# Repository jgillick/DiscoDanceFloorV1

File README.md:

# Disco Dance Floor

This project is for a full-size interactive dance floor that can respond to touch and sound.

The floor is made up of individually controlled squares (nodes) attached to a computer via an
RS485 bus. Each node has an Atmega328 with RGB LEDs and a capacitive sensor to detect someone
standing over that cell.

The master controller uses Node.js and provides a simple API that can be used to
write custom floor control programs.

## More information
More information about the build can be found on my page at [hackaday.io](https://hackaday.io/project/4209-interactive-disco-dance-floor).

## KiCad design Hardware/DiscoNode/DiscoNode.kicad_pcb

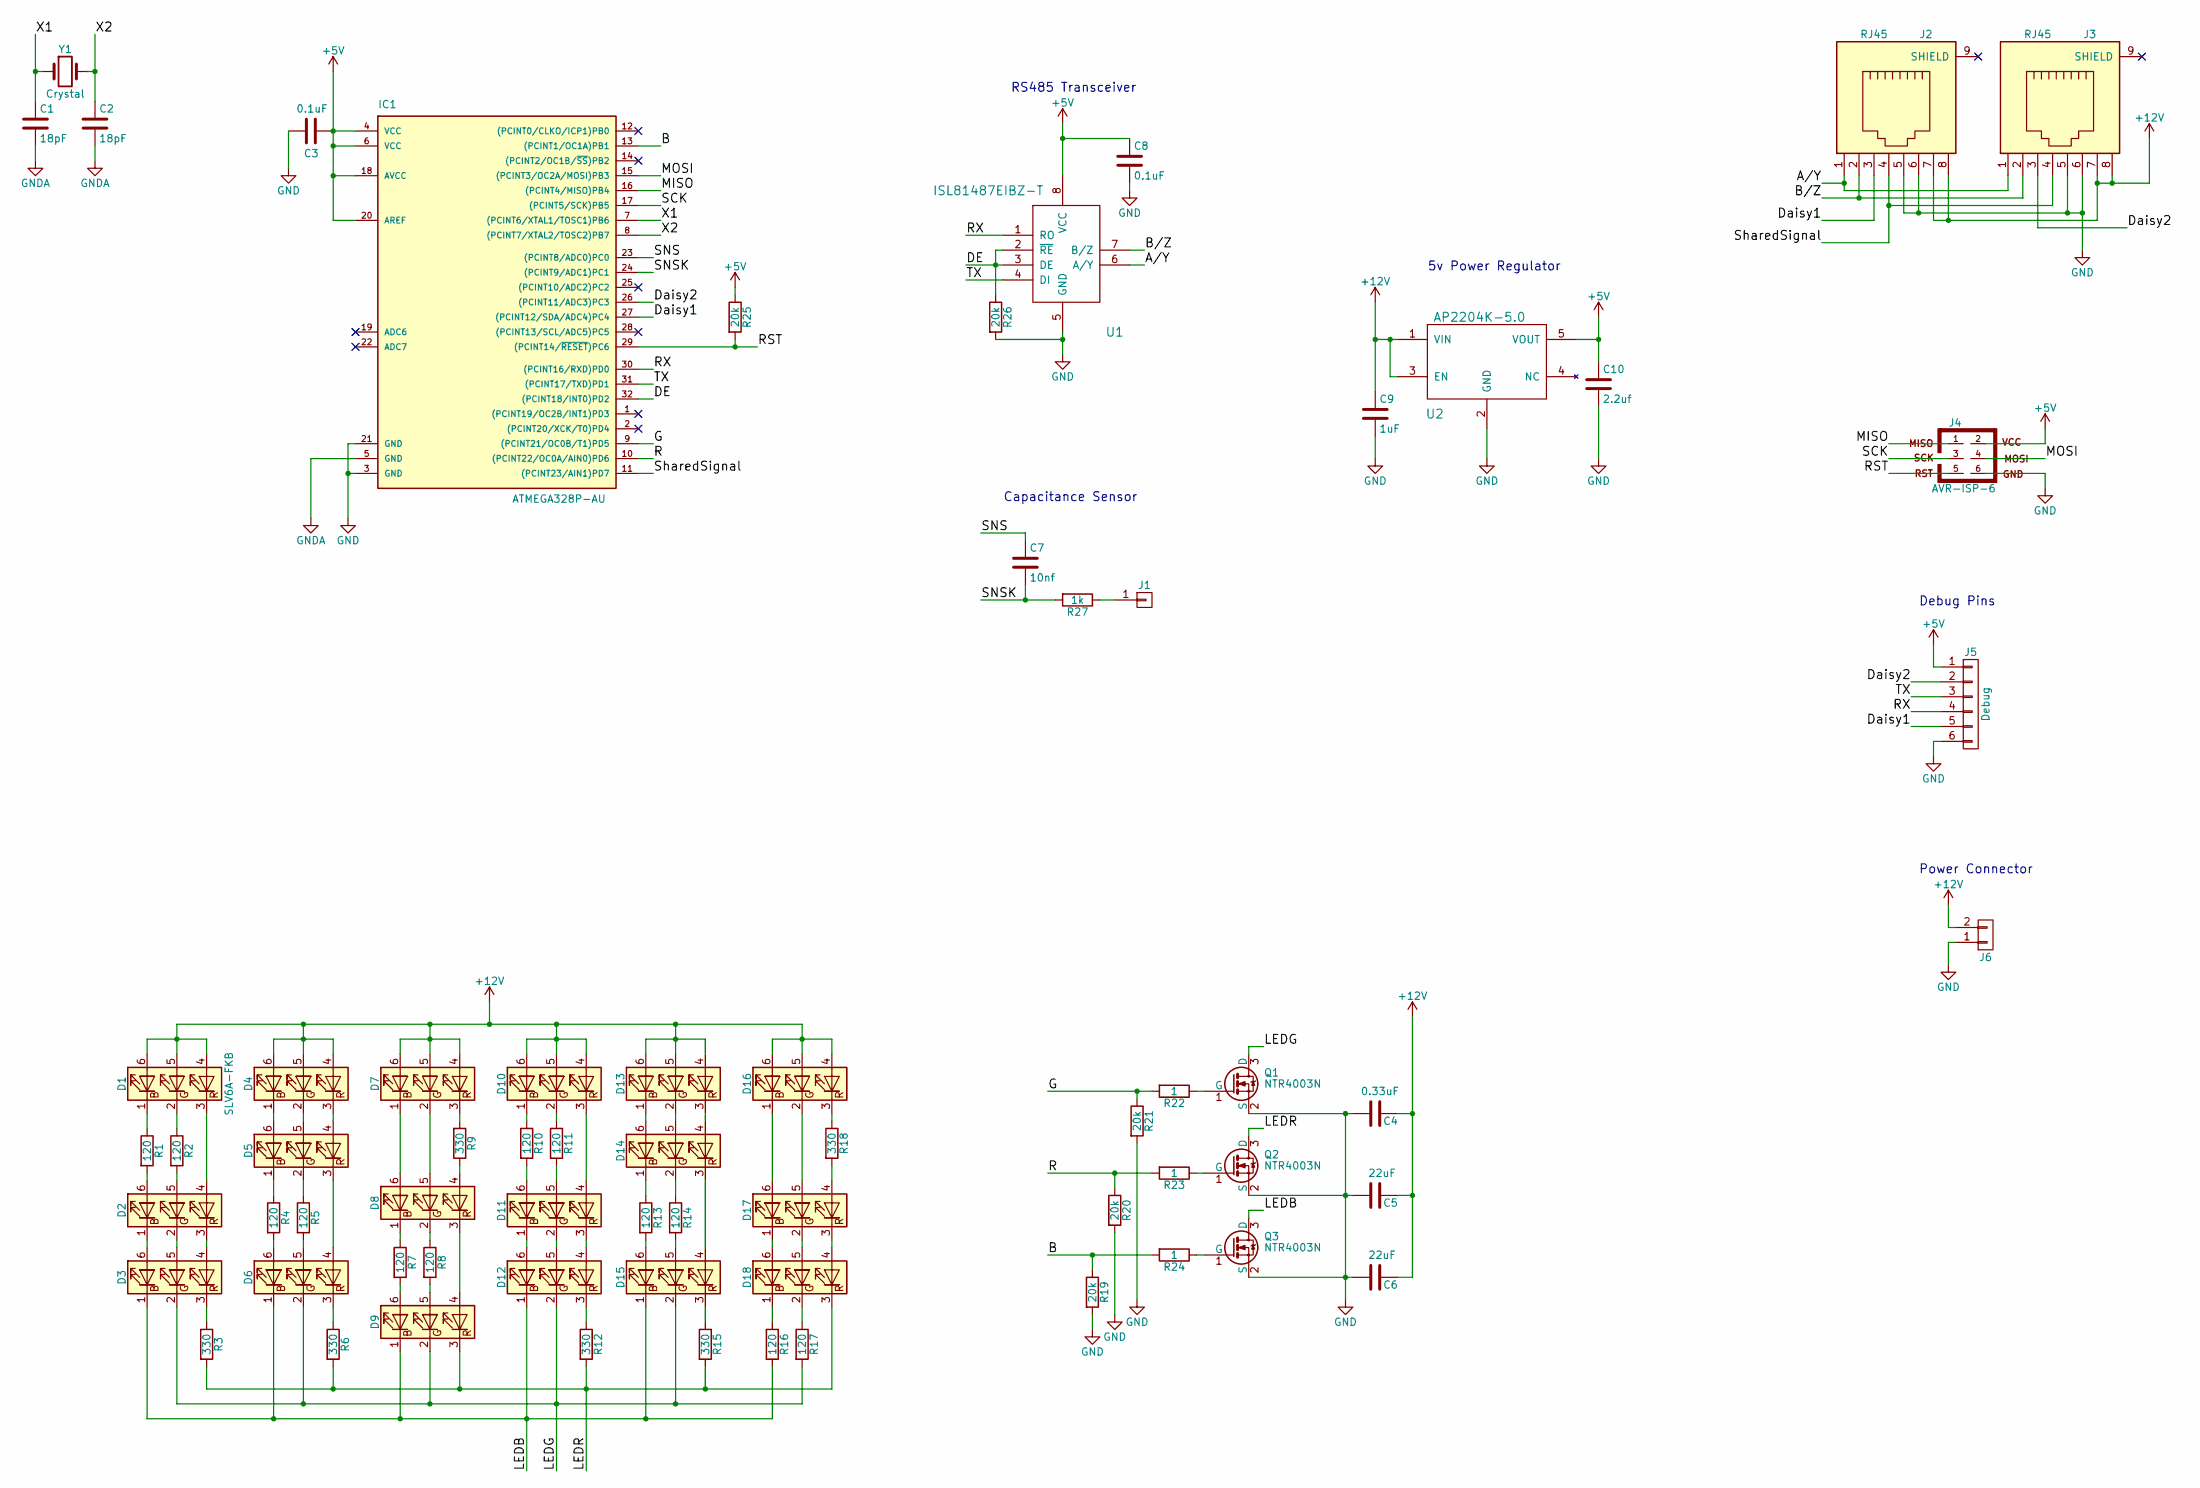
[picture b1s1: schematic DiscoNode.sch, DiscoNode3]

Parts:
C1, C2: 18pF; C_0805; MPN C0805C180J3GACTU; Digikey 399-10065-1-ND
C3, C8: 0.1uF; C_0805; MPN CL21F104ZAANNNC; Digikey 1276-1286-1-ND
C4: 0.33uF; C_0805; MPN CL21B334KAFNNNE; Digikey 1276-1808-1-ND
C5, C6: 22uF; C_1206; MPN GRM31CR61E226ME15K; Digikey 490-14676-1-ND
C7: 10nf; C_0805; MPN GRM216R71E223KA01D; Digikey 490-11558-1-ND
C9: 1uF; C_0805; MPN CL21B105KAFNNNG; Digikey 1276-6469-1-ND
C10: 2.2uf; C_0805; MPN CL21A225KAFNNNG; Digikey 1276-6458-1-ND
D1, D2, D3, D4, D5, D6, D7, D8, D9, D10, D11, D12, D13, D14, D15, D16, D17, D18: SLV6A-FKB; LED_RGB-PLCC6-5.5x5.3mm
IC1: ATMEGA328P-AU; TQFP32
J1: 1267; Keystone_1267_Connector; MPN 1267; Digikey 36-1267-ND
J2, J3: RJ45; RJ45_8; MPN 54602-908LF; Digikey 609-1046-ND
J4: AVR-ISP-6; Pin_Header_Straight_2x03_Pitch2.54mm
J5: Debug; Pin_Header_Straight_1x06_Pitch2.54mm
J6: 0026605020; Molex_26_60_5020; MPN 0026605020; Digikey WM4640-ND
Q1, Q2, Q3: NTR4003N; SOT-23; Digikey NTR4003NT1GOSCT-ND
R1, R2, R4, R7, R10, R13, R16: 120; R_0805; MPN RMCF0805JT120R
R3, R6, R9, R12, R15, R18: 330; R_0805; MPN RMCF0805JT330R
R5, R8, R11, R14, R17: 120; R_0805; MPN RMCF0805JT120R; Digikey RMCF0805JT120RCT-ND
R19, R20, R21, R25, R26: 20k; R_0805; MPN RMCF0805JT20K0; Digikey RMCF0805JT20K0CT-ND
R22, R23, R24: 1; R_0805; MPN RMCF0805JT1R00; Digikey RMCF0805JT1R00CT-ND
R27: 1k; R_0805_HandSoldering; MPN RMCF0805JT1K00; Digikey RMCF0805JT1K00CT-ND
U1: ISL81487EIBZ-T; SOIC-8_3.9x4.9mm_Pitch1.27mm; MPN ISL81487EIBZ-T; Digikey ISL81487EIBZ-TCT-ND
U2: AP2204K-5.0; SOT-23-5; MPN AP2204K-5.0TRG1; Digikey AP2204K-5.0TRG1DITR-ND
Y1: Crystal; Crystal_SMD_2pin_7.0x4.1mm; MPN ABLS7M2-20.000MHZ-D-2Y-T; Digikey 535-12832-2-ND

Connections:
+5V: C3.1, C8.1, C10.1, IC1.4 (VCC), IC1.6 (VCC), IC1.18 (AVCC), IC1.20 (AREF), J4.2, J5.1, R25.1, U1.8 (VCC), U2.5 (VOUT)
+12V: C4.1, C5.1, C6.1, C9.1, D1.4 (BA), D1.5 (GA), D1.6 (RA), D4.4 (BA), D4.5 (GA), D4.6 (RA), D7.4 (BA), D7.5 (GA), D7.6 (RA), D10.4 (BA), D10.5 (GA), D10.6 (RA), D13.4 (BA), D13.5 (GA), D13.6 (RA), D16.4 (BA), D16.5 (GA), D16.6 (RA), J2.7, J2.8, J3.7, J3.8, J6.2, U2.1 (VIN), U2.3 (EN)
/A/Y: J2.1, J3.1, U1.6 (A/Y)
/B: IC1.13 ((PCINT1/OC1A)PB1), R19.1, R24.2
/B/Z: J2.2, J3.2, U1.7 (B/Z)
/DE: IC1.32 ((PCINT18/INT0)PD2), R26.1, U1.2 (~RE), U1.3 (DE)
/Daisy1: IC1.27 ((PCINT12/SDA/ADC4)PC4), J2.3, J5.5
/Daisy2: IC1.26 ((PCINT11/ADC3)PC3), J3.3, J5.2
/G: IC1.9 ((PCINT21/OC0B/T1)PD5), R21.1, R22.2
/LEDB: D3.1 (RK), D6.1 (RK), D9.1 (RK), D12.1 (RK), D15.1 (RK), Q3.3 (D), R16.2
/LEDG: D3.2 (GK), D6.2 (GK), D9.2 (GK), D12.2 (GK), D15.2 (GK), Q1.3 (D), R17.2
/LEDR: D9.3 (BK), D18.3 (BK), Q2.3 (D), R3.2, R6.2, R12.2, R15.2
/MISO: IC1.16 ((PCINT4/MISO)PB4), J4.1
/MOSI: IC1.15 ((PCINT3/OC2A/MOSI)PB3), J4.4
/R: IC1.10 ((PCINT22/OC0A/AIN0)PD6), R20.1, R23.2
/RST: IC1.29 ((PCINT14/~RESET~)PC6), J4.5, R25.2
/RX: IC1.30 ((PCINT16/RXD)PD0), J5.4, U1.1 (RO)
/SCK: IC1.17 ((PCINT5/SCK)PB5), J4.3
/SNS: C7.1, IC1.23 ((PCINT8/ADC0)PC0)
/SNSK: C7.2, IC1.24 ((PCINT9/ADC1)PC1), R27.2
/SharedSignal: IC1.11 ((PCINT23/AIN1)PD7), J2.4, J3.4
/TX: IC1.31 ((PCINT17/TXD)PD1), J5.3, U1.4 (DI)
/X1: C1.1, IC1.7 ((PCINT6/XTAL1/TOSC1)PB6), Y1.1
/X2: C2.1, IC1.8 ((PCINT7/XTAL2/TOSC2)PB7), Y1.2
GND: C3.2, C4.2, C5.2, C6.2, C8.2, C9.2, C10.2, IC1.3 (GND), IC1.21 (GND), J2.5, J2.6, J3.5, J3.6, J4.6, J5.6, J6.1, Q1.2 (S), Q2.2 (S), Q3.2 (S), R19.2, R20.2, R21.2, R26.2, U1.5 (GND), U2.2 (GND)
GNDA: C1.2, C2.2, IC1.5 (GND)
unnamed: D1.1 (RK), R1.1
unnamed: D1.2 (GK), R2.1
unnamed: D1.3 (BK), D2.4 (BA)
unnamed: D2.1 (RK), D3.6 (RA)
unnamed: D2.2 (GK), D3.5 (GA)
unnamed: D2.3 (BK), D3.4 (BA)
unnamed: D2.5 (GA), R2.2
unnamed: D2.6 (RA), R1.2
unnamed: D3.3 (BK), R3.1
unnamed: D4.1 (RK), D5.6 (RA)
unnamed: D4.2 (GK), D5.5 (GA)
unnamed: D4.3 (BK), D5.4 (BA)
unnamed: D5.1 (RK), R4.1
unnamed: D5.2 (GK), R5.1
unnamed: D5.3 (BK), D6.4 (BA)
unnamed: D6.3 (BK), R6.1
unnamed: D6.5 (GA), R5.2
unnamed: D6.6 (RA), R4.2
unnamed: D7.1 (RK), D8.6 (RA)
unnamed: D7.2 (GK), D8.5 (GA)
unnamed: D7.3 (BK), R9.2
unnamed: D8.1 (RK), R7.1
unnamed: D8.2 (GK), R8.1
unnamed: D8.3 (BK), D9.4 (BA)
unnamed: D8.4 (BA), R9.1
unnamed: D9.5 (GA), R8.2
unnamed: D9.6 (RA), R7.2
unnamed: D10.1 (RK), R10.1
unnamed: D10.2 (GK), R11.1
unnamed: D10.3 (BK), D11.4 (BA)
unnamed: D11.1 (RK), D12.6 (RA)
unnamed: D11.2 (GK), D12.5 (GA)
unnamed: D11.3 (BK), D12.4 (BA)
unnamed: D11.5 (GA), R11.2
unnamed: D11.6 (RA), R10.2
unnamed: D12.3 (BK), R12.1
unnamed: D13.1 (RK), D14.6 (RA)
unnamed: D13.2 (GK), D14.5 (GA)
unnamed: D13.3 (BK), D14.4 (BA)
unnamed: D14.1 (RK), R13.1
unnamed: D14.2 (GK), R14.1
unnamed: D14.3 (BK), D15.4 (BA)
unnamed: D15.3 (BK), R15.1
unnamed: D15.5 (GA), R14.2
unnamed: D15.6 (RA), R13.2
unnamed: D16.1 (RK), D17.6 (RA)
unnamed: D16.2 (GK), D17.5 (GA)
unnamed: D16.3 (BK), R18.1
unnamed: D17.1 (RK), D18.6 (RA)
unnamed: D17.2 (GK), D18.5 (GA)
unnamed: D17.3 (BK), D18.4 (BA)
unnamed: D17.4 (BA), R18.2
unnamed: D18.1 (RK), R16.1
unnamed: D18.2 (GK), R17.1
unnamed: J1.1, R27.1
unnamed: Q1.1 (G), R22.1
unnamed: Q2.1 (G), R23.1
unnamed: Q3.1 (G), R24.1

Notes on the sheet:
Capacitance Sensor
RS485 Transceiver
5v Power Regulator
Power Connector
Debug Pins

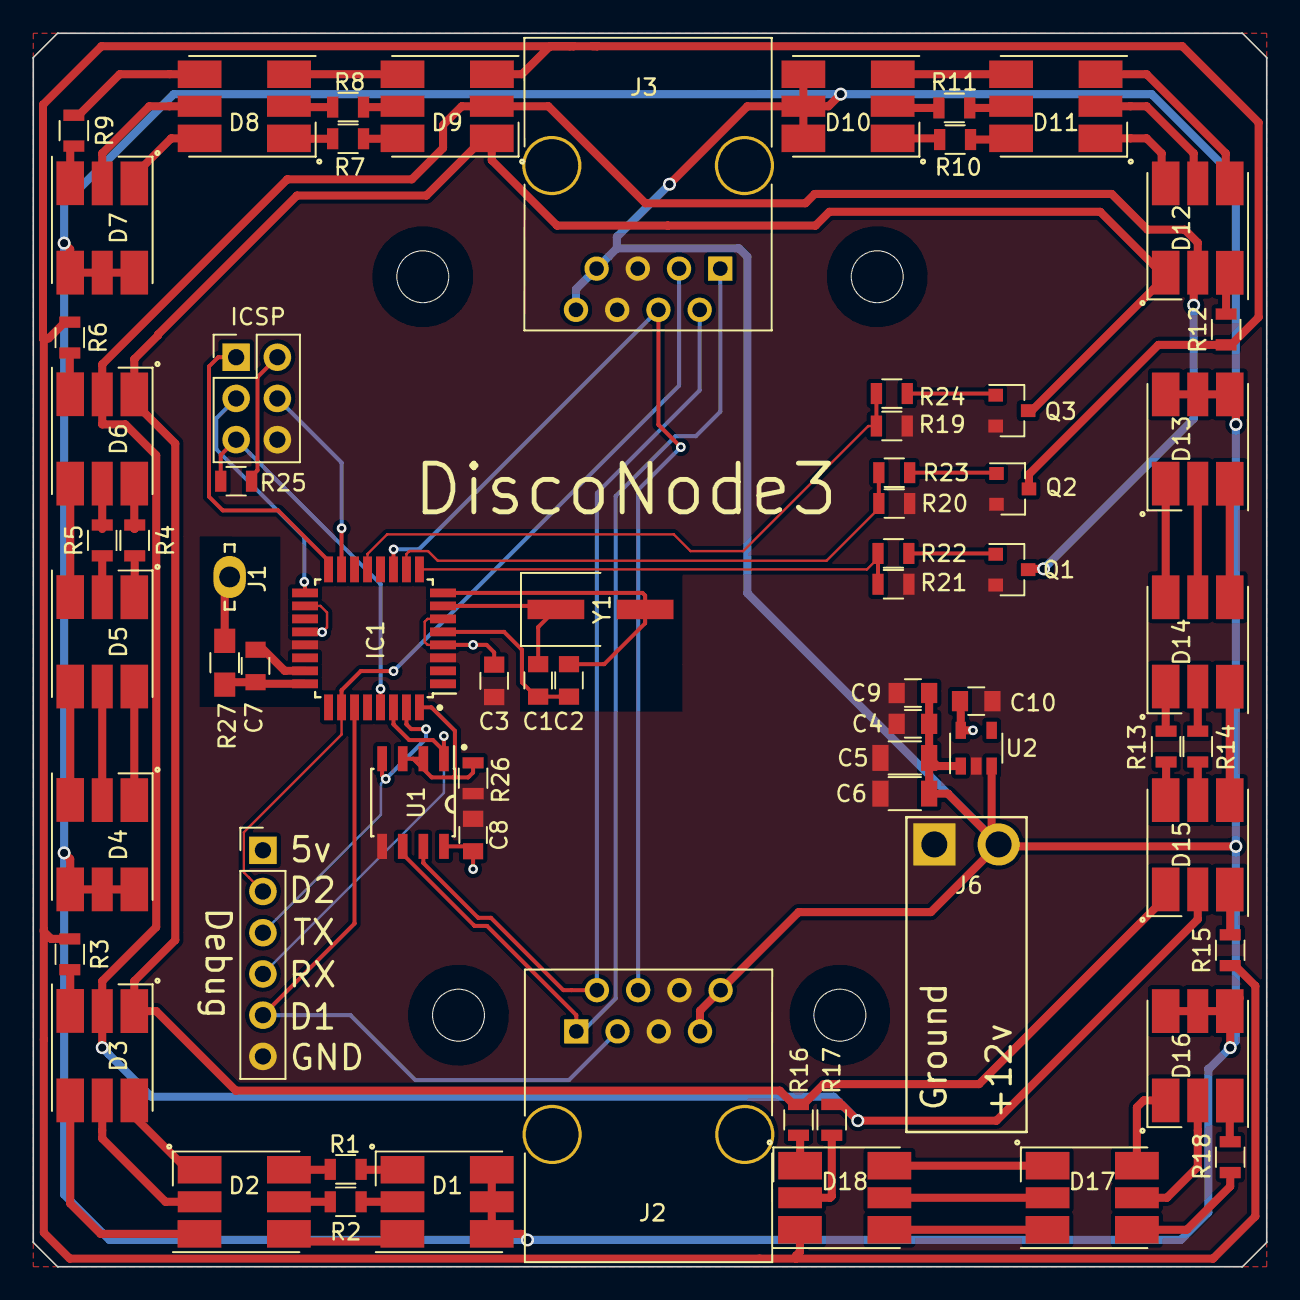
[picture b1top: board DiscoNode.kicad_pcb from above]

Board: 2 copper layers, 76.0 x 76.0 mm, 72 parts (0 on the bottom side), 84 nets.

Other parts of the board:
HOLE: MountingHole_3.2mm_M3
HOLE#2, HOLE#3, HOLE#4: MountingHole_3.2mm_M3

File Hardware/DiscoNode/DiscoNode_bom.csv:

Component,Description,Part,References,Value,Footprint,Quantity Per PCB,Datasheet,MPN,Digikey,MFN
1,Unpolarized capacitor,C,C3 C8,0.1uF,C_0805,2,,CL21F104ZAANNNC,1276-1286-1-ND,
2,Unpolarized capacitor,C,C4,0.33uF,C_0805,1,,CL21B334KAFNNNE,1276-1808-1-ND,
3,Unpolarized capacitor,C,C7,10nf,C_0805,1,,GRM216R71E223KA01D,490-11558-1-ND,
4,Unpolarized capacitor,C,C1 C2,18pF,C_0805,2,,C0805C180J3GACTU,399-10065-1-ND,
5,Unpolarized capacitor,C,C9,1uF,C_0805,1,,CL21B105KAFNNNG,1276-6469-1-ND,
6,Unpolarized capacitor,C,C10,2.2uf,C_0805,1,,CL21A225KAFNNNG,1276-6458-1-ND,
7,Unpolarized capacitor,C,C5 C6,22uF,C_1206,2,,GRM31CR61E226ME15K,490-14676-1-ND,
8,LED RGB 6 pins. Cree SLV6A-FKB,SLV6A-FKB,D1 D2 D3 D4 D5 D6 D7 D8 D9 D10 D11 D12 D13 D14 D15 D16 D17 D18,SLV6A-FKB,LED_RGB-PLCC6-5.5x5.3mm,18,,,,
9,"TQFP32, 16k Flash, 1kB SRAM, 512B EEPROM",ATMEGA328P-AU,IC1,ATMEGA328P-AU,,1,http://www.atmel.com/images/atmel-8271-8-bit-avr-microcontro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,,,
10,"Connector, single row, 01x02, pin header",CONN_01X02,J6,0026605020,Molex_26_60_5020,1,,0026605020,WM4640-ND,"Molex, LLC"
11,"Connector, single row, 01x01, pin header",CONN_01X01,J1,1267,Keystone_1267_Connector,1,,1267,36-1267-ND,Keystone Electronics
12,"Standard IDC6 Male Connector, ATMEL ISP 6pin",AVR-ISP-6,J4,AVR-ISP-6,Pin_Header_Straight_2x03_Pitch2.54mm,1,,,,
13,"Connector, single row, 01x06, pin header",CONN_01X06,J5,Debug,Pin_Header_Straight_1x06_Pitch2.54mm,1,,,,
14,RJ45 connector with shield,RJ45,J2 J3,RJ45,RJ45_8,2,,54602-908LF,609-1046-ND,
15,"60V Vds 0.5A Id, N-Channel MOSFET, SOT-23",MMBF170,Q1 Q2 Q3,NTR4003N,SOT-23,3,http://www.fairchildsemi.com/ds/BS/BS170.pdf,,NTR4003NT1GOSCT-ND,NTR4003NT1G
16,Resistor,R,R22 R23 R24,1,R_0805,3,,RMCF0805JT1R00,RMCF0805JT1R00CT-ND,
17,Resistor,R,R2 R3 R5 R6 R8 R9 R11 R12 R14 R15 R17 R18,120,R_0805,12,,RMCF0805JT120R,RMCF0805JT120RCT-ND,
18,Resistor,R,R27,1k,R_0805_HandSoldering,1,,RMCF0805JT1K00,RMCF0805JT1K00CT-ND,
19,Resistor,R,R19 R20 R21 R25 R26,20k,R_0805,5,,RMCF0805JT20K0,RMCF0805JT20K0CT-ND,
20,Resistor,R,R1 R4 R7 R10 R13 R16,330,R_0805,6,,RMCF0805JT330R,RMCF0805JT330RCT-ND,
21,,AP2204K-5.0,U2,AP2204K-5.0,SOT-23-5,1,,AP2204K-5.0TRG1,AP2204K-5.0TRG1DITR-ND,
22,,ISL81487E,U1,ISL81487EIBZ-T,SOIC-8_3.9x4.9mm_Pitch1.27mm,1,,ISL81487EIBZ-T,ISL81487EIBZ-TCT-ND,Intersil
23,Two pin crystal,Crystal,Y1,Crystal,Crystal_SMD_2pin_7.0x4.1mm,1,,ABLS7M2-20.000MHZ-D-2Y-T,535-12832-2-ND,





Component Groups:,23
Component Count:,68
Fitted Components:,68
Number of PCBs:,1
Total components:,68
Schematic Version:,3
Schematic Date:,
BoM Date:,"Monday, May 15, 2017 'AMt' 09:28:01 AM"
Schematic Source:,/Users/Jeremy/Projects/DiscoDanceFloor/Hardware/DiscoNode/DiscoNode.sch
KiCad Version:,Eeschema 4.0.6

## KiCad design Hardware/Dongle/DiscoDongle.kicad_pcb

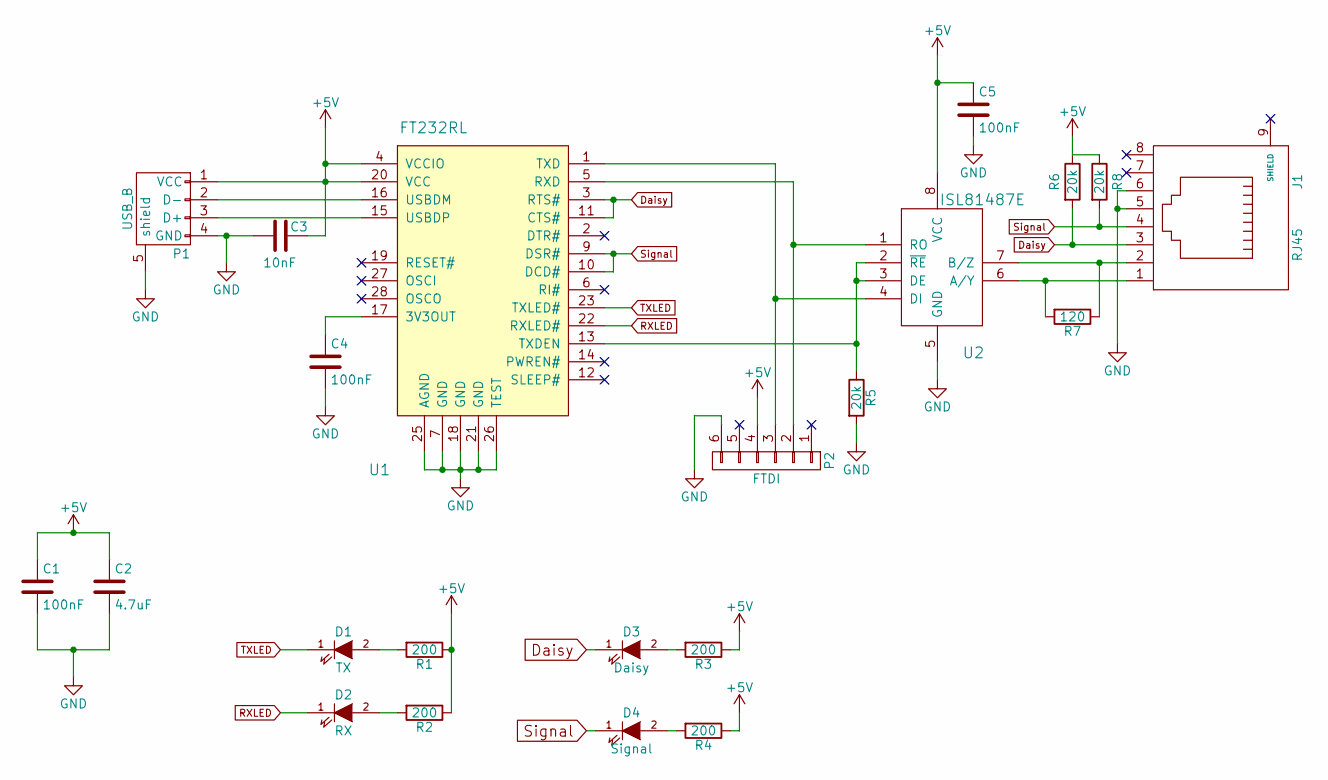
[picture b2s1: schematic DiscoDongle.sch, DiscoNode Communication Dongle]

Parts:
C1, C4, C5: 100nF; C_0805
C2: 4.7uF; C_0805
C3: 10nF; C_0805
D1: TX; LED_0805
D2: RX; LED_0805
D3: Daisy; LED_0805
D4: Signal; LED_0805
J1: RJ45; RJ45_8
P1: USB_B
P2: FTDI; Pin_Header_Straight_1x06
R1, R2, R3, R4: 200; R_0805
R5, R6, R8: 20k; R_0805
R7: 120; R_0805
U1: FT232RL; SSOP-28_5.3x10.2mm_Pitch0.65mm
U2: ISL81487E; SOIC-8_3.9x4.9mm_Pitch1.27mm

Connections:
+5V: C1.1, C2.1, C3.1, C5.1, P1.1 (VCC), P2.4, R1.1, R2.1, R3.1, R4.1, R6.1, R8.1, U1.4 (VCCIO), U1.20 (VCC), U2.8 (VCC)
Daisy: D3.1 (K), J1.3, R6.2, U1.3 (RTS#), U1.11 (CTS#)
GND: C1.2, C2.2, C3.2, C4.2, C5.2, J1.5, J1.6, P1.4 (GND), P1.5 (shield), P2.6, R5.2, U1.7 (GND), U1.18 (GND), U1.21 (GND), U1.25 (AGND), U1.26 (TEST), U2.5 (GND)
unnamed: C4.1, U1.17 (3V3OUT)
unnamed: D1.2 (A), R1.2
unnamed: D2.2 (A), R2.2
unnamed: D3.2 (A), R3.2
unnamed: D4.2 (A), R4.2
unnamed: J1.1, R7.2, U2.6 (A/Y)
unnamed: J1.2, R7.1, U2.7 (B/Z)
unnamed: P1.2 (D-), U1.16 (USBDM)
unnamed: P1.3 (D+), U1.15 (USBDP)
unnamed: P2.2, U1.5 (RXD), U2.1 (RO)
unnamed: P2.3, U1.1 (TXD), U2.4 (DI)
unnamed: R5.1, U1.13 (TXDEN), U2.2 (~RE), U2.3 (DE)
RXLED: D2.1 (K), U1.22 (RXLED#)
Signal: D4.1 (K), J1.4, R8.2, U1.9 (DSR#), U1.10 (DCD#)
TXLED: D1.1 (K), U1.23 (TXLED#)

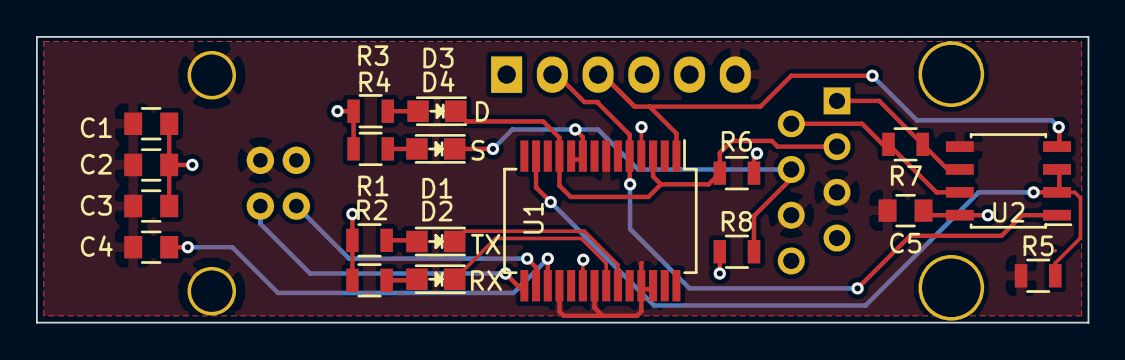
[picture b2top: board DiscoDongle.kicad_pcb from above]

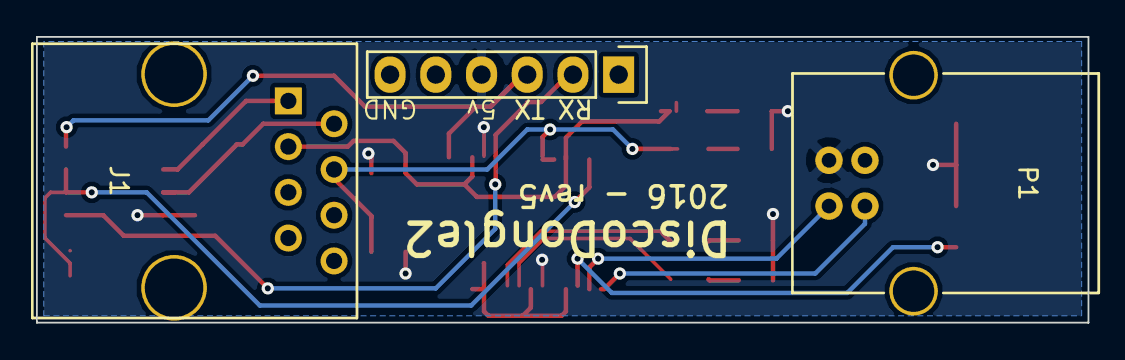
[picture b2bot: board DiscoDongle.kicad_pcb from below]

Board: 2 copper layers, 58.4 x 15.9 mm, 22 parts (3 on the bottom side), 18 nets.

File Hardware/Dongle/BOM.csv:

"Id","Designator","Package","Quantity","Designation","Supplier and ref",
1,"J1","RJ45_8",1,"RJ45",,,
2,"P1","USB_B",1,"USB_B",,,
3,"D2","LED_0805",1,"RX",,,
4,"D1","LED_0805",1,"TX",,,
5,"R1,R2,R4,R3","R_0805",4,"200",,,
6,"C1,C4,C5","C_0805",3,"100nF",,,
7,"C2","C_0805",1,"4.7uF",,,
8,"C3","C_0805",1,"10nF",,,
9,"D3","LED_0805",1,"D",,,
10,"D4","LED_0805",1,"S",,,
11,"R5,R6,R8","R_0805",3,"20k",,,
12,"R7","R_0805",1,"120",,,
13,"U1","SSOP-28_5.3x10.2mm_Pitch0.65mm",1,"FT232RL",,,
14,"U2","SOIC-8_3.9x4.9mm_Pitch1.27mm",1,"ISL81487E",,,

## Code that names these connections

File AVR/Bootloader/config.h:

/*****************************************************************************
*
* Configuration settings for the bootloader
*
****************************************************************************/

#ifndef CONFIG_H
#define CONFIG_H


////////////////////////////////////////////
/// Activate booloader by EEPROM
////////////////////////////////////////////

// Enter programming mode when the EEPROM value
// at address EEPROM_RUN_APP is not 1
#define BOOTLOAD_ON_EEPROM 1

// EEPROM Address
#define EEPROM_RUN_APP (uint8_t*) 3


////////////////////////////////////////////
/// Activate bootloader by pin
////////////////////////////////////////////

// Enter programming mode when a pin matches
// the on/off value defined by BOOTLOAD_PIN_VAL (1 = HIGH)
#define BOOTLOAD_ON_PIN   0
#define BOOTLOAD_PIN_NUM  PD2
#define BOOTLOAD_PIN_DDR  DDRD
#define BOOTLOAD_PIN_REG  PIND
#define BOOTLOAD_PIN_VAL  1


////////////////////////////////////////////
/// Versioning
////////////////////////////////////////////

// The version stored in EEPROM will be compared to the
// version sent to the bootloader. If they're the same, the
// device will skip programming.
#define USE_VERSIONING 0

// The EEPROM address of where the major and minimum version numbers
// are stored. These need to be stored by your program, the bootloader
// does not write to these locations.
#define VERSION_MAJOR (uint8_t*) 4
#define VERSION_MINOR (uint8_t*) 5


////////////////////////////////////////////
/// Signal Line
////////////////////////////////////////////

#define SIGNAL_BIT PD7
#define SIGNAL_DDR_REG DDRD
#define SIGNAL_PIN_REG PIND


////////////////////////////////////////////
/// Communications
////////////////////////////////////////////

#define SERIAL_BAUD 250000
// #define SERIAL_BAUD 115200

////////////////////////////////////////////
/// Bus Message Commands
////////////////////////////////////////////

// Start programming
#define MSG_CMD_PROG_START 0xF1

// Receive the next page number
#define MSG_CMD_PAGE_NUM   0xF2

// Receive the next page of data
#define MSG_CMD_PAGE_DATA  0xF3

// Finish programming and start the main program
#define MSG_CMD_PROG_END   0xF4

#endif

////////////////////////////////////////////
/// Status LEDs
////////////////////////////////////////////

#define OK_LED  PD5
#define OK_DDR  DDRD
#define OK_PORT PORTD

#define WRITE_LED   PB1
#define WRITE_DDR   DDRB
#define WRITE_PORT  PORTB

#define ERROR_LED   PD6
#define ERROR_DDR   DDRD
#define ERROR_PORT  PORTD

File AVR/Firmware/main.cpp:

/*******************************************************************************
* A single disco sqare node.
*
* This program connects to a multi-drop network as a slave node and
* waits for the master node to ask it to check the touch sensor and to set the color
* of the RGB LED.
******************************************************************************/

#include <avr/io.h>
#include <avr/wdt.h>
#include <avr/eeprom.h>

#include "pwm.h"
#include "clock.h"
#include "touch.h"
#include "touch_control.h"
#include "touch_api.h"
#include "MultidropSlave.h"
#include "MultidropData485.h"
#include "version.h"

/*----------------------------------------------------------------------------
                                prototypes
----------------------------------------------------------------------------*/

void comm_init();
void comm_run();
void handle_message();
void handle_response_msg(uint8_t command, uint8_t *buff,uint8_t len);
void set_color(uint8_t *rgb);
void read_sensor();

/*----------------------------------------------------------------------------
                                constants
----------------------------------------------------------------------------*/

#define BUS_BAUD 250000
#define DEFAULT_DETECT_THRES 11u

// Message commands
#define CMD_BOOTLOADER       0xF0  // jump to bootloader for reprogramming
#define CMD_RESET_ADDRESS    0xFA  // reset address
#define CMD_SET_ADDRESS      0xFB

#define CMD_GET_VERSION       0xA0
#define CMD_SET_COLOR         0xA1
#define CMD_CHECK_SENSOR      0xA2
#define CMD_SEND_SENSOR_VALUE 0xA3

#define CMD_SET_DETECT_THRESH 0xB0 // Set the QTouch detection threshold


/*----------------------------------------------------------------------------
                          EEPROM byte addresses
----------------------------------------------------------------------------*/

// Since node addresses can go up to 0xFF and EEPROM default values are 0xFF,
// we need to have an extra byte to tell us if the address has been set.
#define EEPROM_HAS_ADDR        (uint8_t*) 0
#define EEPROM_ADDR            (uint8_t*) 1
#define EEPROM_DETECT_THRESH   (uint8_t*) 2

// Bootloader programming flag (set to 0 to program)
#define EEPROM_SKIP_BOOTLOADER (uint8_t*) 3

// Firmware version
#define EEPROM_VERSION_MAJOR   (uint8_t*) 4
#define EEPROM_VERSION_MINOR   (uint8_t*) 5

/*----------------------------------------------------------------------------
                          global variables
----------------------------------------------------------------------------*/

// The last touch sensor value
uint8_t sensor_value = 0;
uint8_t reading_sensor = 0;

// Bus serial
MultidropData485 serial(PD2, &DDRD, &PORTD);
MultidropSlave comm(&serial);

/*----------------------------------------------------------------------------
                              program
----------------------------------------------------------------------------*/

/**
 * Main program
 */
int main() {
  wdt_disable();
  wdt_enable(WDTO_2S);

  DDRB |= (1 << PB2); // debug LED

  start_clock();
  comm_init();
  pwm_init();

  // Setup touch sensor
  uint8_t detect_threshold = eeprom_read_byte(EEPROM_DETECT_THRESH);
  if (detect_threshold == 0xFF) {
    detect_threshold = DEFAULT_DETECT_THRES;
  }
  touch_init(detect_threshold);

  // Program is okay, skip bootloader next time
  eeprom_update_byte(EEPROM_SKIP_BOOTLOADER, 1);
  eeprom_update_byte(EEPROM_VERSION_MAJOR, FIRMWARE_VERSION_MAJOR);
  eeprom_update_byte(EEPROM_VERSION_MINOR, FIRMWARE_VERSION_MINOR);

  // Program loop
  while(1) {
    wdt_reset();
    comm_run();
  }
}

/**
 * Initialize the serial communication bus.
 */
void comm_init() {
  // enable pull-up on RX pin
  PORTD |= (1 << PD0);

  serial.begin(BUS_BAUD);

  // Define daisy chain lines and let polarity (next/previous) be determined at runtime
  comm.addDaisyChain(PC3, &DDRC, &PORTC, &PINC,
                     PC4, &DDRC, &PORTC, &PINC);

  // Response message handler
  comm.setResponseHandler(&handle_response_msg);

  // Check if we have an address in the EEPROM
  uint8_t addr = eeprom_read_byte(EEPROM_ADDR);
  if (addr > 0 && eeprom_read_byte(EEPROM_HAS_ADDR) == 1) {
    comm.setAddress(addr);
  }
}

/**
 * Read the next bytes from the communication bus and handle any messages.
 */
void comm_run() {
  comm.read();
  if (comm.hasNewMessage() && comm.isAddressedToMe()) {
    handle_message();
  }
}

/**
 * Handle a new message received from the bus.
 */
void handle_message() {
  switch (comm.getCommand()) {
    // We've been assigned an address
    case CMD_SET_ADDRESS:
      if (comm.getAddress() > 0) {
        eeprom_update_byte(EEPROM_HAS_ADDR, 1);
        eeprom_update_byte(EEPROM_ADDR, comm.getAddress());
      }
    break;

    // Reset address saved in the eeprom
    case CMD_RESET_ADDRESS:
      eeprom_update_byte(EEPROM_HAS_ADDR, 0);
      eeprom_update_byte(EEPROM_ADDR, 0);
    break;

    // Set the LED color
    case CMD_SET_COLOR:
      if (comm.getDataLen() == 3) {
        set_color(comm.getData());
      }
    break;

    // Check the touch sensor
    case CMD_CHECK_SENSOR:
      read_sensor();
    break;

    // Set the touch sensor detect threshold
    case CMD_SET_DETECT_THRESH:
      if (comm.getDataLen() == 1) {
        uint8_t dt = comm.getData()[0];
        eeprom_update_byte(EEPROM_DETECT_THRESH, dt);
        touch_init(dt);
      }
    break;

    // Reboot the device into the bootloader
    case CMD_BOOTLOADER:
      eeprom_update_byte(EEPROM_SKIP_BOOTLOADER, 0xFF);
      wdt_enable(WDTO_15MS);
      while(1);
    break;
  }
}

/**
 * Answer response messages from the bus.
 */
void handle_response_msg(uint8_t command, uint8_t *buff, uint8_t len) {
  switch (comm.getCommand()) {
    // Return our firmware version number
    case CMD_GET_VERSION:
      if (len >= 2) {
        buff[0] = FIRMWARE_VERSION_MAJOR;
        buff[1] = FIRMWARE_VERSION_MINOR;
      }
    break;

    // Send the last sensor value received
    case CMD_SEND_SENSOR_VALUE:
      if (len >= 1) {
        buff[0] = sensor_value;
      }
    break;
  }
}

/**
 * Update RGB LED values
 */
void set_color(uint8_t *rgb) {
  red_pwm(rgb[0]);
  green_pwm(rgb[1]);
  blue_pwm(rgb[2]);
}

/**
 * Get a new reading from the touch sensor.
 */
void read_sensor() {
  if (reading_sensor) return;
  reading_sensor = 1;

  // Default MCU register value
  uint8_t mcuRegister = MCUCR;
  uint16_t status_flag = 0u;

  do {
    // Disable pull-ups
    MCUCR |= (1 << PUD);

    // Measure sensor
    status_flag = qt_measure_sensors( millis() );

    // Reset pull-ups
    MCUCR = mcuRegister;

    // Check bus before next measurement
    comm_run();
  } while (status_flag & QTLIB_BURST_AGAIN); // check again, if burst flag is set

  // Get sensor value
  sensor_value = GET_SENSOR_STATE(0);
  reading_sensor = 0;

  // Debug LED
  if (sensor_value) {
    PORTB |= (1 << PB2);
  } else {
    PORTB &= ~(1 << PB2);
  }
}

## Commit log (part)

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2015-03-07 Add initial prototype
2015-03-07 Add README
2015-03-07 Add link to RS485 chip
2015-03-07 Fix problem where node stops listening as soon as another node is addressed by removing address filtering from MessageBuffer (still not sure why this was happening
2015-03-07 Move ACK response code. Comment out extra debugging
2015-03-07 Change to 9600 baud
2015-03-08 Update README with Test Master flow
2015-03-08 Update README headers
2015-03-08 Update README rs485 transcever wiring
2015-03-08 Add 'status' phase to master/nodes communication process
2015-03-08 Add status phase
2015-03-08 Move back to status phase after running program once
2015-03-09 Change pin numbers to support capacitive touch sensor
2015-03-09 Cleanup debugging statements
2015-03-09 Add capacitive touch program
2015-03-10 Add message checksum
2015-03-10 Remove unneeded debugging. Change type to getType()
2015-03-11 remove cache from source control
2015-03-12 Add reset command. Add target color to node status message
2015-03-12 Update header to be fixed width
2015-03-13 Don't put node_modules in source control
2015-03-13 Add more instructions
2015-03-13 Turn off the SASS watcher and compile once on load. Otherwise the watcher does not shutdown when the app closes
2015-03-13 Add serial setup dialog
2015-03-13 gitignore
2015-03-13 AVR readme
2015-03-13 Add fader library
2015-03-13 Remove log file
2015-03-13 Add underscore and serialport
2015-03-13 Remove compiled CSS
2015-03-13 compiled stylesheets
2015-03-13 Add message character escaping.
2015-03-13 Add message buffer escaping
2015-03-13 Use to prevent a deep stack track / recusion
2015-03-13 Actually use nexttick this time
2015-03-13 Process header before looking for the end of a message
2015-03-13 do not commit compiled css
2015-03-13 Integrate connecting and loading floor cells into the UI
2015-03-13 jslint cleanup
2015-03-13 nw is now NW.js
2015-03-16 Add support for running a program
2015-03-16 Make the dimensions area a status area
2015-03-16 Don't destroy objects every time the floor refreshes, and other updates
2015-03-16 Comments and helper methods
2015-03-16 Update initiating a connected floor
2015-03-16 Update node/cell syncing code
2015-03-16 Update status color order
2015-03-16 jshint update
2015-03-16 Dialog UI. Add some color (now if I could actually get a designer)
2015-03-17 Fix support for escaped characters in bus messages
2015-03-17 Increase baud and general cleanup.
2015-03-17 Wait for program shutdown before starting the next one. Add `changeAllCells` method
2015-03-17 General cleanup and code optimization
2015-03-17 Change emulated floor color conversion to lighten at under 30% brightness
2015-03-17 Adjust program fade timing
2015-03-17 Rename controller folder
2015-03-17 Update main read
2015-03-18 Pre-fetch sensor readings to not block status response.
2015-03-21 Change object style (util.inherits doesn't work well with prototype object literal)
2015-03-21 Focus window and add frame rate
2015-03-21 Message timeout and debugging
2015-03-23 remove debugging
2015-03-23 Fix `autoSetDimensions()` for a non-even number of cells
2015-03-23 Move full buffer debug arrays
2015-03-24 Filter messages that are not for us or master
2015-03-24 Update debugging
2015-03-26 Break out Test Master from the main pin map
2015-03-26 Add circuit diagram images
2015-03-26 Update RGB LED labels
2015-03-26 Add Fritzing file
2015-03-30 Move fuse bit section to disco node project
2015-03-30 Add fuse bit section to README
2015-03-30 Update BOM
2015-03-30 Add sensor threshold to constants
2015-03-30 Add test program
2015-03-30 Remove deprecated constants
2015-05-08 Add program info to 'info' object
2015-05-08 Rename Flaming Steps to Step Trails
2015-05-09 Add 'Saturday Night Fever' program!
2015-05-22 Add new non-blocking capacitive sensing library
2015-05-22 Remove timer macros
2015-05-23 Improve stability of data (especially filtered data). Also some house cleaning.
2015-05-23 Add configurable threshold value
2015-06-08 Dynamic baseline calibration and other cleanup
2015-06-10 Floor structure updates * Move pass throughs to be at the end of the slots * Remove dowel pin holes * Change hole & pin to tongue and groove.
2015-06-10 Add code to do a better job of adjusting the baseline and other general cleanup.
2015-06-19 Convert to using input capture method with kalman filter for sensor detection.
2015-06-20 Remove unused code. Update main comment.
2015-06-20 Integrate new cap sensor lib
2015-07-10 Create new AVR C native RGB fading library
2015-07-13 Update to support a 20 Mhz clock
2015-07-20 Misc optimizations
2015-07-27 Add wrap utility function.
2015-07-27 Change timing of random colors program
2015-07-27 Fix shutdown issues with saturday night fever
2015-07-27 Step tails should fade
2015-07-27 Misc style updates
2015-07-27 Program filtering and a "Play All" mode!
2015-07-27 Add audio reactive floor programs!!!
2015-07-27 Refine programs a bit
2015-07-28 More audio programs
2015-07-28 Move program code to it's own controller. Add stop button Add program descriptions as tooltips
2015-07-28 Better filtering
2015-07-29 Add crc node library
2015-07-29 Gracefully close serial port
2015-07-29 Cleanup and stub out streaming response
2015-07-29 Update time between charging sensor
2015-07-29 Add tongue and groove
2015-07-29 Update to new message format
2015-07-29 Add option to show program list
2015-07-31 Get streaming responses working on the AVR
2015-07-31 Use query animate instead of FadeLoop
2015-07-31 Update communication protocol to support streaming responses and command IDs
2015-07-31 Update timer interrupt code
2015-08-07 Enable new RGB fader. Update message buffer to support streaming response
2015-08-07 Update fuse command
2015-08-10 Remove space from folder name
2015-08-10 Add query UI
2015-08-12 Move javascript files
2015-08-12 Move SASS compilation to load with app
2015-08-12 Move JS files
2015-08-13 Add batch update and handle color fading on the master.
2015-08-14 Make audio bars animate smoother
2015-08-17 No more data line polarity! The data direction will be detected at runtime. Other optimizations.
2015-08-17 Disconnect things on quit
2015-08-17 Update cell management
2015-08-17 Add close methods
2015-08-17 Update command codes
2015-08-23 Send batch updates in batches of 50 bytes (due to Arduino's 64 byte serial buffer)
2015-08-23 Enable 'reset' toggle
2015-09-09 Add support for command line options.
2015-09-09 Put audio connection in a promise
2015-09-09 Add disconnect button. Fix color fading with `updateFadeFrame()`. Other code restructuring and cleanup
2015-09-09 Add Rain program
2016-02-08 Extract some of RS485 code.
2016-02-08 Updated construction models
2016-02-08 Font awesome fonts
2016-02-08 Font awesome to base
2016-02-08 Config file
2016-04-25 New Disco Controller on Electron
2016-04-25 Add read. Change tmpl to html
2016-04-26 Add settings and connection pages. Setup app packaging commands.
2016-04-26 UI Tweaks
2016-04-29 Add gulp build/dist scripts. Convert TypeScript to ES6 JavaScript (with annotations & decorators)
2016-04-29 Make button text bigger.
2016-04-29 Add windows dist task to gulp
2016-04-30 Add app section to read.
2016-04-30 Remove webpack and many other gulp stories.
2016-04-30 Build out settings, with persistent data storage.
2016-05-02 Build floor automatically. Create settings service.
2016-05-03 Floor and program list UI
2016-05-03 Fix floor sizing
2016-05-06 Upgrade to angular RC1
2016-05-06 FloorCellList and IProgram
2016-05-06 Move code under src/app/ folder and add new shared folder.
2016-05-07 More name changing.
2016-05-07 Add change observer to storage
2016-05-07 Get programs start/stop working.
2016-05-28 Add compiled files to git ignore.
2016-05-28 Add program timeout
2016-05-28 Fix program timeouts.
2016-05-29 Show indicator for long starting or stopping of a program.
2016-05-30 Add fade controller
2016-05-31 Copy color arrays before using them. Fix initial program fade. Kill fade promise after a program is stopped.
2016-06-05 Add audio libraries and optimize program controller service.
2016-06-06 Convert programs to typescript with class decorator.
2016-06-20 Update the DiscoDongle with more LEDs and pull-up on daisy line.
2016-06-20 Initial serial communication work.
2016-06-20 Start porting the Multi-drop Bus Protocol to node.
2016-06-22 Tie the RE and DE together on the TXEN line of FTDI
2016-06-22 Create bus terminator.
2016-06-22 Get bus/serial services talking to the bus.
2016-06-22 Fix wiring to TXEN and pull-down resistor
2016-06-22 Adjust baud
2016-06-27 More work to get the floor talking.
2016-06-28 Connect to floor. Use observables in bus protocol service.
2016-06-30 Add support for object dot notation in storage keys.
2016-06-30 Start building out the communication run loop.
2016-06-30 Fix race condition and data length error.
2016-06-30 Add frames per second indicator.
2016-07-03 Bootloader dreaming...
2016-07-04 DiscoDongle - Rev5 - Move components to bottom.
2016-07-04 Build out response message processing.
2016-07-06 Add emulated touch sensors by clicking on floor cells.
2016-07-06 Make sure random colors have at least 1 value over 100.
2016-07-06 Turn floor cell list into an iterator.
2016-07-06 Pass fading property through cell object.
2016-07-06 Add random number function to program utils.
2016-07-09 Firmware works! (sets the LEDs and reports back the sensor value)
2016-07-09 Fixed support for bus response messages
2016-07-10 Adjust touch sensor sensitivity and lower false positives.
2016-07-10 Fix re-addressing. Don't checksum on message start characters (0xFF 0xFF)
2016-07-10 Enable "Keep same addresses" connection feature.
2016-07-10 Save node address to EEPROM
2016-07-12 Fix program loop running faster for every stop/start
2016-07-12 Fade to black after stopping a program
2016-07-12 Fully port primaries program over
2016-07-12 Update package
2016-07-12 Remove mediastream
2016-07-12 Upgrade angular to rc 4
2016-07-12 Upgrade router and forms
2016-07-15 Add optional max value to randomColor()
2016-07-15 Create the Game of Life program.
2016-07-18 Fix random colors function
2016-07-18 Change baud and timeouts
2016-07-18 Add detect threshold setting command. Update baud to 250000
2016-08-02 Rename DiscoController2 to DiscoController
2016-08-02 Touch sensor tuning
2016-08-02 Add support for shuffle and continuous play mode ('play all')
2016-08-02 Add auto play and attempt to handle program errors.
2016-08-02 Update white/black distribution
2016-08-08 Update install instructions.
2016-08-08 Save known device list to settings.
2016-08-08 Make program controller take full window height.
2016-08-08 Remove 'clean' as a build prereq
2016-08-08 Update tsconfig
2016-08-08 Safely load program list
2016-08-08 Remove `ENVIRONMENT` variable
2016-08-08 Save settings to user directory
2016-08-11 Port audio bars program
2016-08-11 Add 'disabled' flag to programs
2016-08-11 Remove old code
2016-08-11 Add rings program
2016-08-11 Remove debugging.
2016-08-11 Tweak rain
2016-08-11 Fix bugs with the Rings program
2016-08-12 Fix program timer in play all mode.
2016-08-12 Only check sensors for interactive programs.
2016-08-12 Fix error with skipping sensor checks
2016-08-13 Fix app versions
2016-08-13 Skip step with a timeout
2016-08-13 Unhide menu
2016-08-14 Connection fixes
2016-08-15 Adjust skip timing
2016-08-15 Optimize sending color on the bus
2016-08-15 Enable response timeout
2016-08-15 Set cell table once, no need for binding
2016-08-15 Take the floor cell painting out of the angular bindings.
2016-08-15 Simplify
2016-08-15 Paint floor with change observers
2016-08-16 Add setting to disable floor preview
2016-08-16 Enable production mode
2016-08-17 Update app icon
2016-08-18 Remove launcher
2016-08-18 Fix node addressing
2016-08-18 Words are hard
2016-08-18 Add startup screen and add support for auto connect.
2016-08-20 Update dimensions when connected to the floor.
2016-08-21 Hide checkbox while connecting.
2016-09-20 Add "lines" program
2016-09-29 Simplify daily/signal connections. Remove FTDI headers.
2016-09-29 Remove arduino directory
2017-04-16 Fix LEDs
2017-04-17 Update LED & Crystal footprints. Change LED resistor placement.
2017-05-10 Move RJ45 jacks to edge of board.
2017-05-15 Updated parts
2017-05-15 Move parts around. Better LED layout. Move RJ45 jacks to edge of board
2017-06-26 Move debug pins.
2017-06-26 Fix USB position.
